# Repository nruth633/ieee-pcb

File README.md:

# IEEE LED Cube Board

KiCad design for one slice of the LED matrix cube that the University of Denver IEEE
chapter is building as a group project. Three daisy-chained 74HCT595 shift registers drive
24 MMBT3904 low-side switches, which gives eight RGB columns from a five-wire bus (CLK,
DATA, LATCH, BLANK, GND).

Write-up: https://nruth633.github.io/projects/ieee-cube.html

Open `ieee.kicad_pro` in KiCad 10.

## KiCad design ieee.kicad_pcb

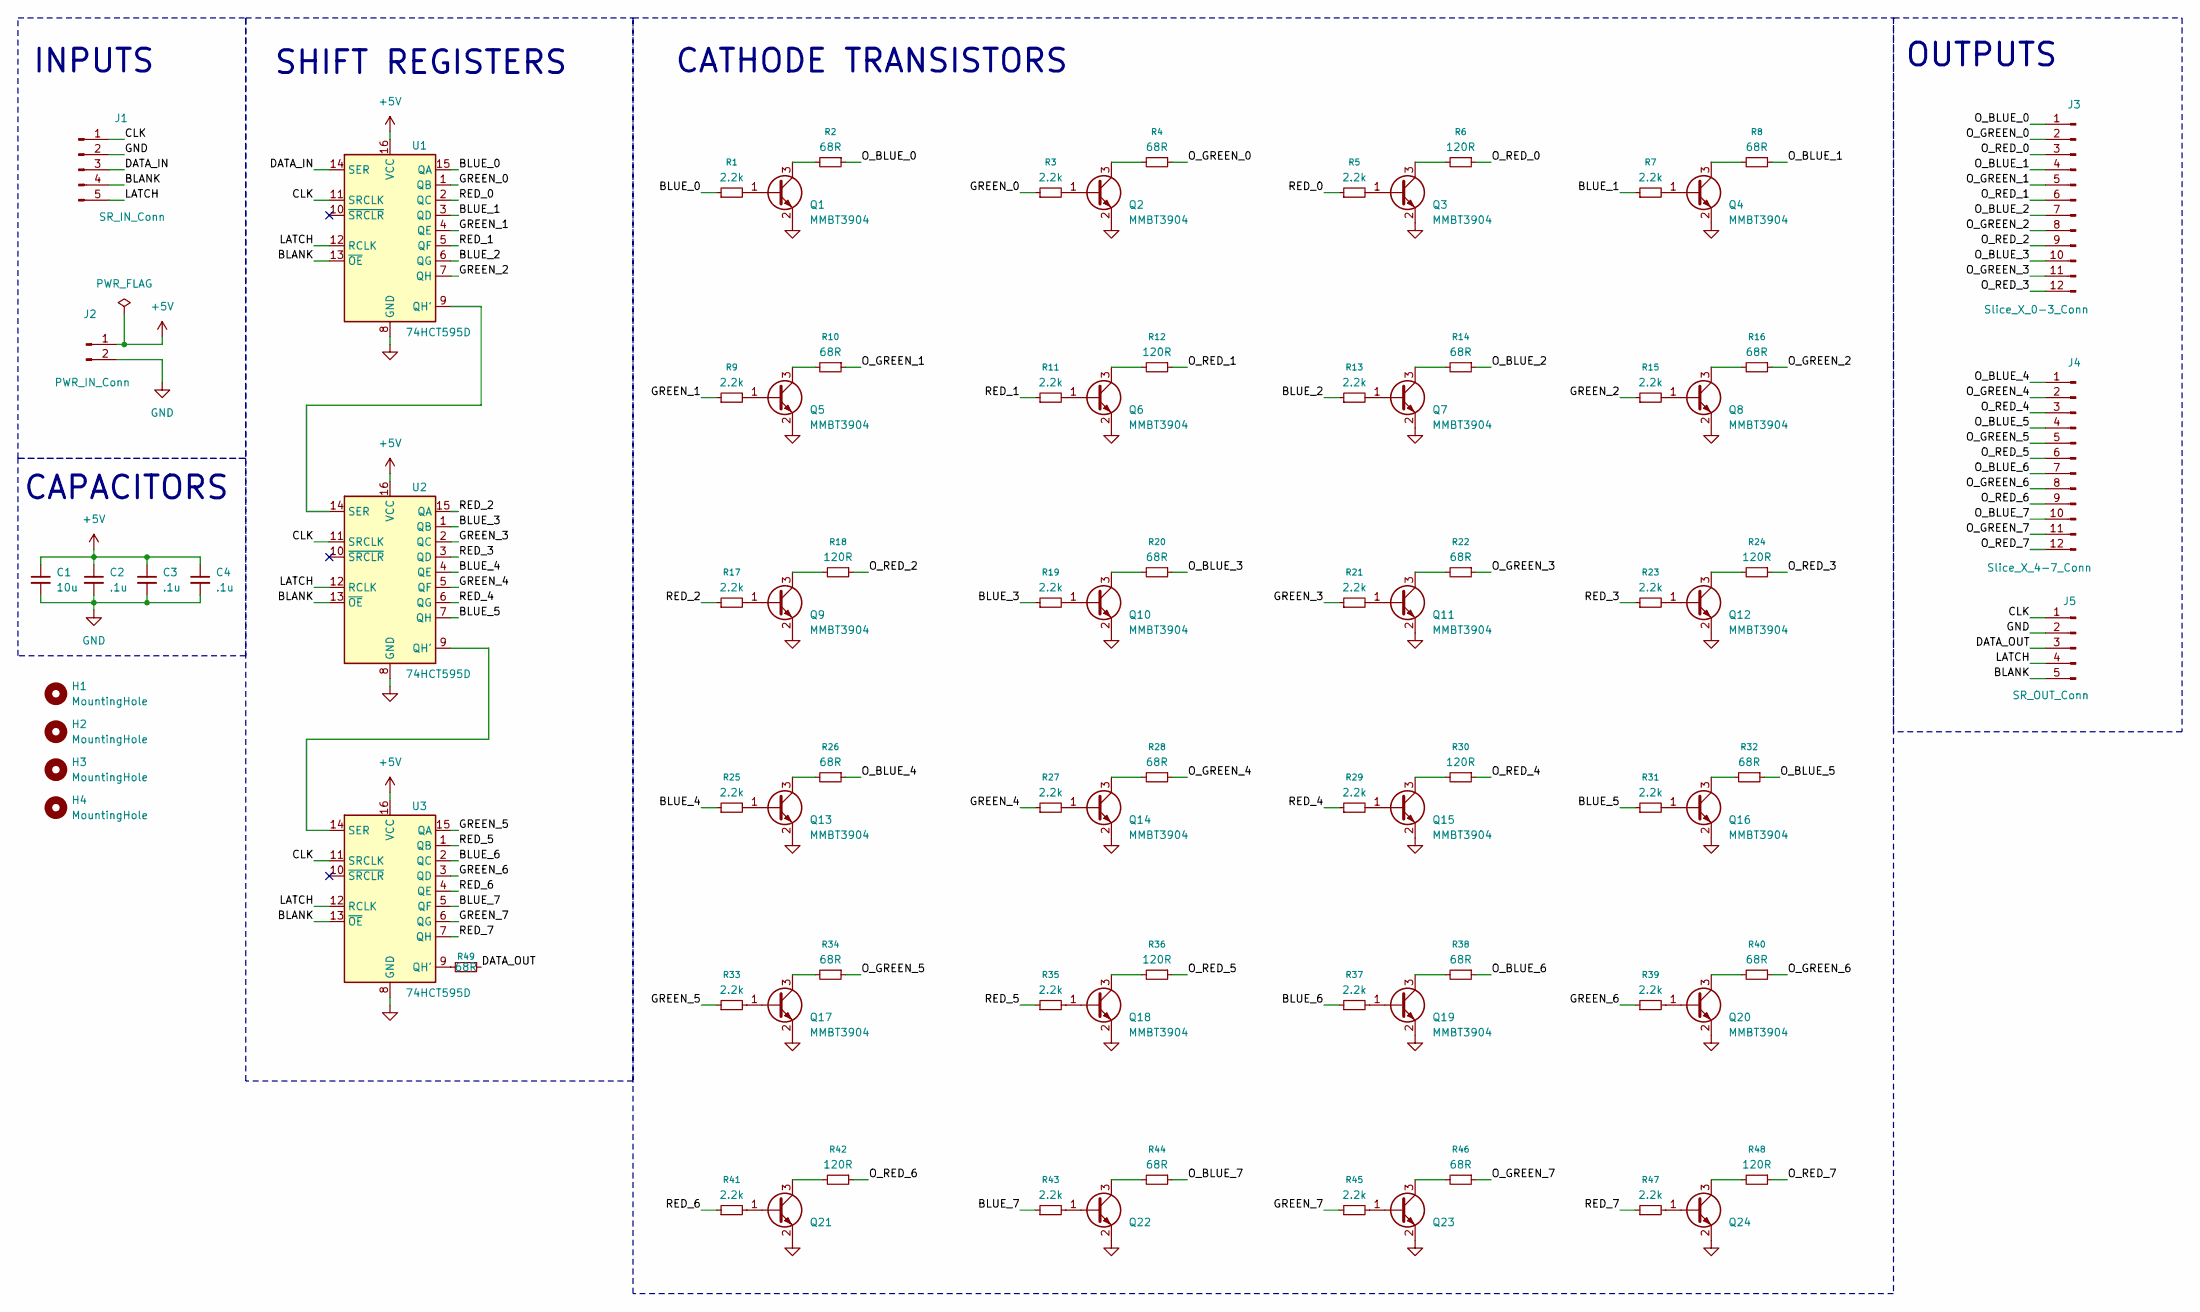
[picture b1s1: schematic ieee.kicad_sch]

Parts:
C1: 10u; C_0805_2012Metric_Pad1.18x1.45mm_HandSolder; Mfr # MCASL21GBB7106KTNA01
C2, C3, C4: .1u; C_0805_2012Metric_Pad1.18x1.45mm_HandSolder; Mfr # KAF21BR71H104JM
H1, H2, H3, H4: MountingHole; MountingHole_3.2mm_M3
J1: SR_IN_Conn; JST_PH_B5B-PH-K_1x05_P2.00mm_Vertical; Mfr # B5B-PH-K-S(LF)(SN)
J2: PWR_IN_Conn; JST_XH_B2B-XH-A_1x02_P2.50mm_Vertical; Mfr # B2B-XH-A
J3: Slice_X_0-3_Conn; JST_PH_B12B-PH-K_1x12_P2.00mm_Vertical; Mfr # B12B-PH-K-S
J4: Slice_X_4-7_Conn; JST_PH_B12B-PH-K_1x12_P2.00mm_Vertical; Mfr # B12B-PH-K-S
J5: SR_OUT_Conn; JST_PH_B5B-PH-K_1x05_P2.00mm_Vertical; Mfr # B5B-PH-K-S(LF)(SN)
Q1, Q2, Q3, Q4, Q5, Q6, Q7, Q8, Q9, Q10, Q11, Q12, Q13, Q14, Q15, Q16, Q17, Q18, Q19, Q20, Q21, Q22, Q23, Q24: MMBT3904; SOT-23; Mfr # 750-MMBT3904-G
R1, R3, R5, R7, R9, R11, R13, R15, R17, R19, R21, R23, R25, R27, R29, R31, R33, R35, R37, R39, R41, R43, R45, R47: 2.2k; R_0805_2012Metric_Pad1.20x1.40mm_HandSolder; Mfr # 0805W8J0222T5E
R2, R4, R8, R10, R14, R16, R20, R22, R26, R28, R32, R34, R38, R40, R44, R46, R49: 68R; R_0805_2012Metric_Pad1.20x1.40mm_HandSolder; Mfr # 0805W8J0680T5E
R6, R12, R18, R24, R30, R36, R42, R48: 120R; R_0805_2012Metric_Pad1.20x1.40mm_HandSolder; Mfr # RT0805FRE13120RL
U1, U2, U3: 74HCT595D; SOIC-16_3.9x9.9mm_P1.27mm; Mfr # 74HCT595D,118

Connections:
+5V: C1.1, C2.1, C3.1, C4.1, J2.1, U1.16 (VCC), U2.16 (VCC), U3.16 (VCC)
/BLANK: J1.4, J5.5, U1.13 (~OE), U2.13 (~OE), U3.13 (~OE)
/BLUE_0: R1.1, U1.15 (QA)
/BLUE_1: R7.1, U1.3 (QD)
/BLUE_2: R13.1, U1.6 (QG)
/BLUE_3: R19.1, U2.1 (QB)
/BLUE_4: R25.1, U2.4 (QE)
/BLUE_5: R31.1, U2.7 (QH)
/BLUE_6: R37.1, U3.2 (QC)
/BLUE_7: R43.1, U3.5 (QF)
/CLK: J1.1, J5.1, U1.11 (SRCLK), U2.11 (SRCLK), U3.11 (SRCLK)
/DATA_IN: J1.3, U1.14 (SER)
/DATA_OUT: J5.3, R49.1
/GREEN_0: R3.1, U1.1 (QB)
/GREEN_1: R9.1, U1.4 (QE)
/GREEN_2: R15.1, U1.7 (QH)
/GREEN_3: R21.1, U2.2 (QC)
/GREEN_4: R27.1, U2.5 (QF)
/GREEN_5: R33.1, U3.15 (QA)
/GREEN_6: R39.1, U3.3 (QD)
/GREEN_7: R45.1, U3.6 (QG)
/LATCH: J1.5, J5.4, U1.12 (RCLK), U2.12 (RCLK), U3.12 (RCLK)
/O_BLUE_0: J3.1, R2.1
/O_BLUE_1: J3.4, R8.1
/O_BLUE_2: J3.7, R14.1
/O_BLUE_3: J3.10, R20.1
/O_BLUE_4: J4.1, R26.1
/O_BLUE_5: J4.4, R32.1
/O_BLUE_6: J4.7, R38.1
/O_BLUE_7: J4.10, R44.1
/O_GREEN_0: J3.2, R4.1
/O_GREEN_1: J3.5, R10.1
/O_GREEN_2: J3.8, R16.1
/O_GREEN_3: J3.11, R22.1
/O_GREEN_4: J4.2, R28.1
/O_GREEN_5: J4.5, R34.1
/O_GREEN_6: J4.8, R40.1
/O_GREEN_7: J4.11, R46.1
/O_RED_0: J3.3, R6.1
/O_RED_1: J3.6, R12.1
/O_RED_2: J3.9, R18.1
/O_RED_3: J3.12, R24.1
/O_RED_4: J4.3, R30.1
/O_RED_5: J4.6, R36.1
/O_RED_6: J4.9, R42.1
/O_RED_7: J4.12, R48.1
/RED_0: R5.1, U1.2 (QC)
/RED_1: R11.1, U1.5 (QF)
/RED_2: R17.1, U2.15 (QA)
/RED_3: R23.1, U2.3 (QD)
/RED_4: R29.1, U2.6 (QG)
/RED_5: R35.1, U3.1 (QB)
/RED_6: R41.1, U3.4 (QE)
/RED_7: R47.1, U3.7 (QH)
GND: C1.2, C2.2, C3.2, C4.2, J1.2, J2.2, J5.2, Q1.2 (E), Q2.2 (E), Q3.2 (E), Q4.2 (E), Q5.2 (E), Q6.2 (E), Q7.2 (E), Q8.2 (E), Q9.2 (E), Q10.2 (E), Q11.2 (E), Q12.2 (E), Q13.2 (E), Q14.2 (E), Q15.2 (E), Q16.2 (E), Q17.2 (E), Q18.2 (E), Q19.2 (E), Q20.2 (E), Q21.2 (E), Q22.2 (E), Q23.2 (E), Q24.2 (E), U1.8 (GND), U2.8 (GND), U3.8 (GND)
unnamed: Q1.1 (B), R1.2
unnamed: Q1.3 (C), R2.2
unnamed: Q2.1 (B), R3.2
unnamed: Q2.3 (C), R4.2
unnamed: Q3.1 (B), R5.2
unnamed: Q3.3 (C), R6.2
unnamed: Q4.1 (B), R7.2
unnamed: Q4.3 (C), R8.2
unnamed: Q5.1 (B), R9.2
unnamed: Q5.3 (C), R10.2
unnamed: Q6.1 (B), R11.2
unnamed: Q6.3 (C), R12.2
unnamed: Q7.1 (B), R13.2
unnamed: Q7.3 (C), R14.2
unnamed: Q8.1 (B), R15.2
unnamed: Q8.3 (C), R16.2
unnamed: Q9.1 (B), R17.2
unnamed: Q9.3 (C), R18.2
unnamed: Q10.1 (B), R19.2
unnamed: Q10.3 (C), R20.2
unnamed: Q11.1 (B), R21.2
unnamed: Q11.3 (C), R22.2
unnamed: Q12.1 (B), R23.2
unnamed: Q12.3 (C), R24.2
unnamed: Q13.1 (B), R25.2
unnamed: Q13.3 (C), R26.2
unnamed: Q14.1 (B), R27.2
unnamed: Q14.3 (C), R28.2
unnamed: Q15.1 (B), R29.2
unnamed: Q15.3 (C), R30.2
unnamed: Q16.1 (B), R31.2
unnamed: Q16.3 (C), R32.2
unnamed: Q17.1 (B), R33.2
unnamed: Q17.3 (C), R34.2
unnamed: Q18.1 (B), R35.2
unnamed: Q18.3 (C), R36.2
unnamed: Q19.1 (B), R37.2
unnamed: Q19.3 (C), R38.2
unnamed: Q20.1 (B), R39.2
unnamed: Q20.3 (C), R40.2
unnamed: Q21.1 (B), R41.2
unnamed: Q21.3 (C), R42.2
unnamed: Q22.1 (B), R43.2
unnamed: Q22.3 (C), R44.2
unnamed: Q23.1 (B), R45.2
unnamed: Q23.3 (C), R46.2
unnamed: Q24.1 (B), R47.2
unnamed: Q24.3 (C), R48.2
unnamed: U1.9 (QH'), U2.14 (SER)
unnamed: U2.9 (QH'), U3.14 (SER)
unnamed: R49.2, U3.9 (QH')

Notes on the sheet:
INPUTS
CATHODE TRANSISTORS
SHIFT REGISTERS
OUTPUTS
CAPACITORS

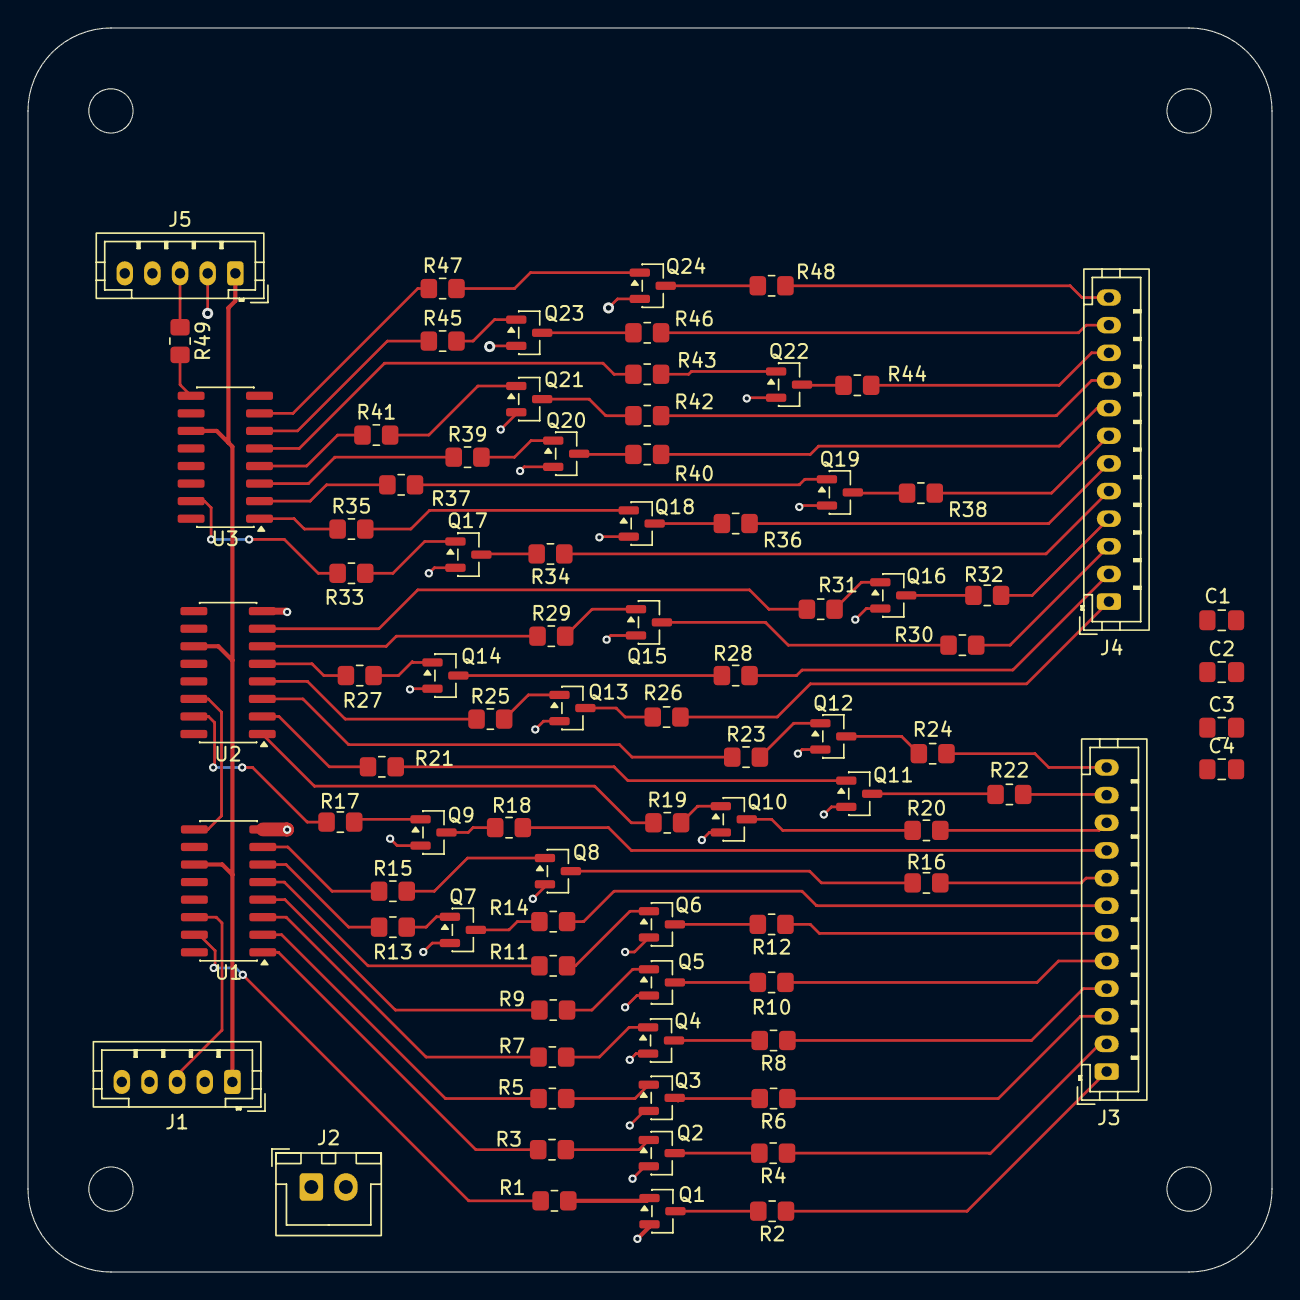
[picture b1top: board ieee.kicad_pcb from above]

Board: 2 copper layers, 90.0 x 90.0 mm, 89 parts (0 on the bottom side), 106 nets.
